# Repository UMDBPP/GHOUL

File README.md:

# GHOUL

Repository for the GHOUL project started in Fall 2022 as a part of the National Eclipse Ballooning Project

(A spooky spiritual sucessor to Helios)

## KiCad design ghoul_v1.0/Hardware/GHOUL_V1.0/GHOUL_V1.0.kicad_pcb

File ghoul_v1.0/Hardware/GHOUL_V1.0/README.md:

View in your browser: https://kicanvas.org/?github=https%3A%2F%2Fgithub.com%2FUMDBPP%2FGHOUL%2Ftree%2Fmain%2Fghoul_v1.0%2FHardware%2FGHOUL_V1.0

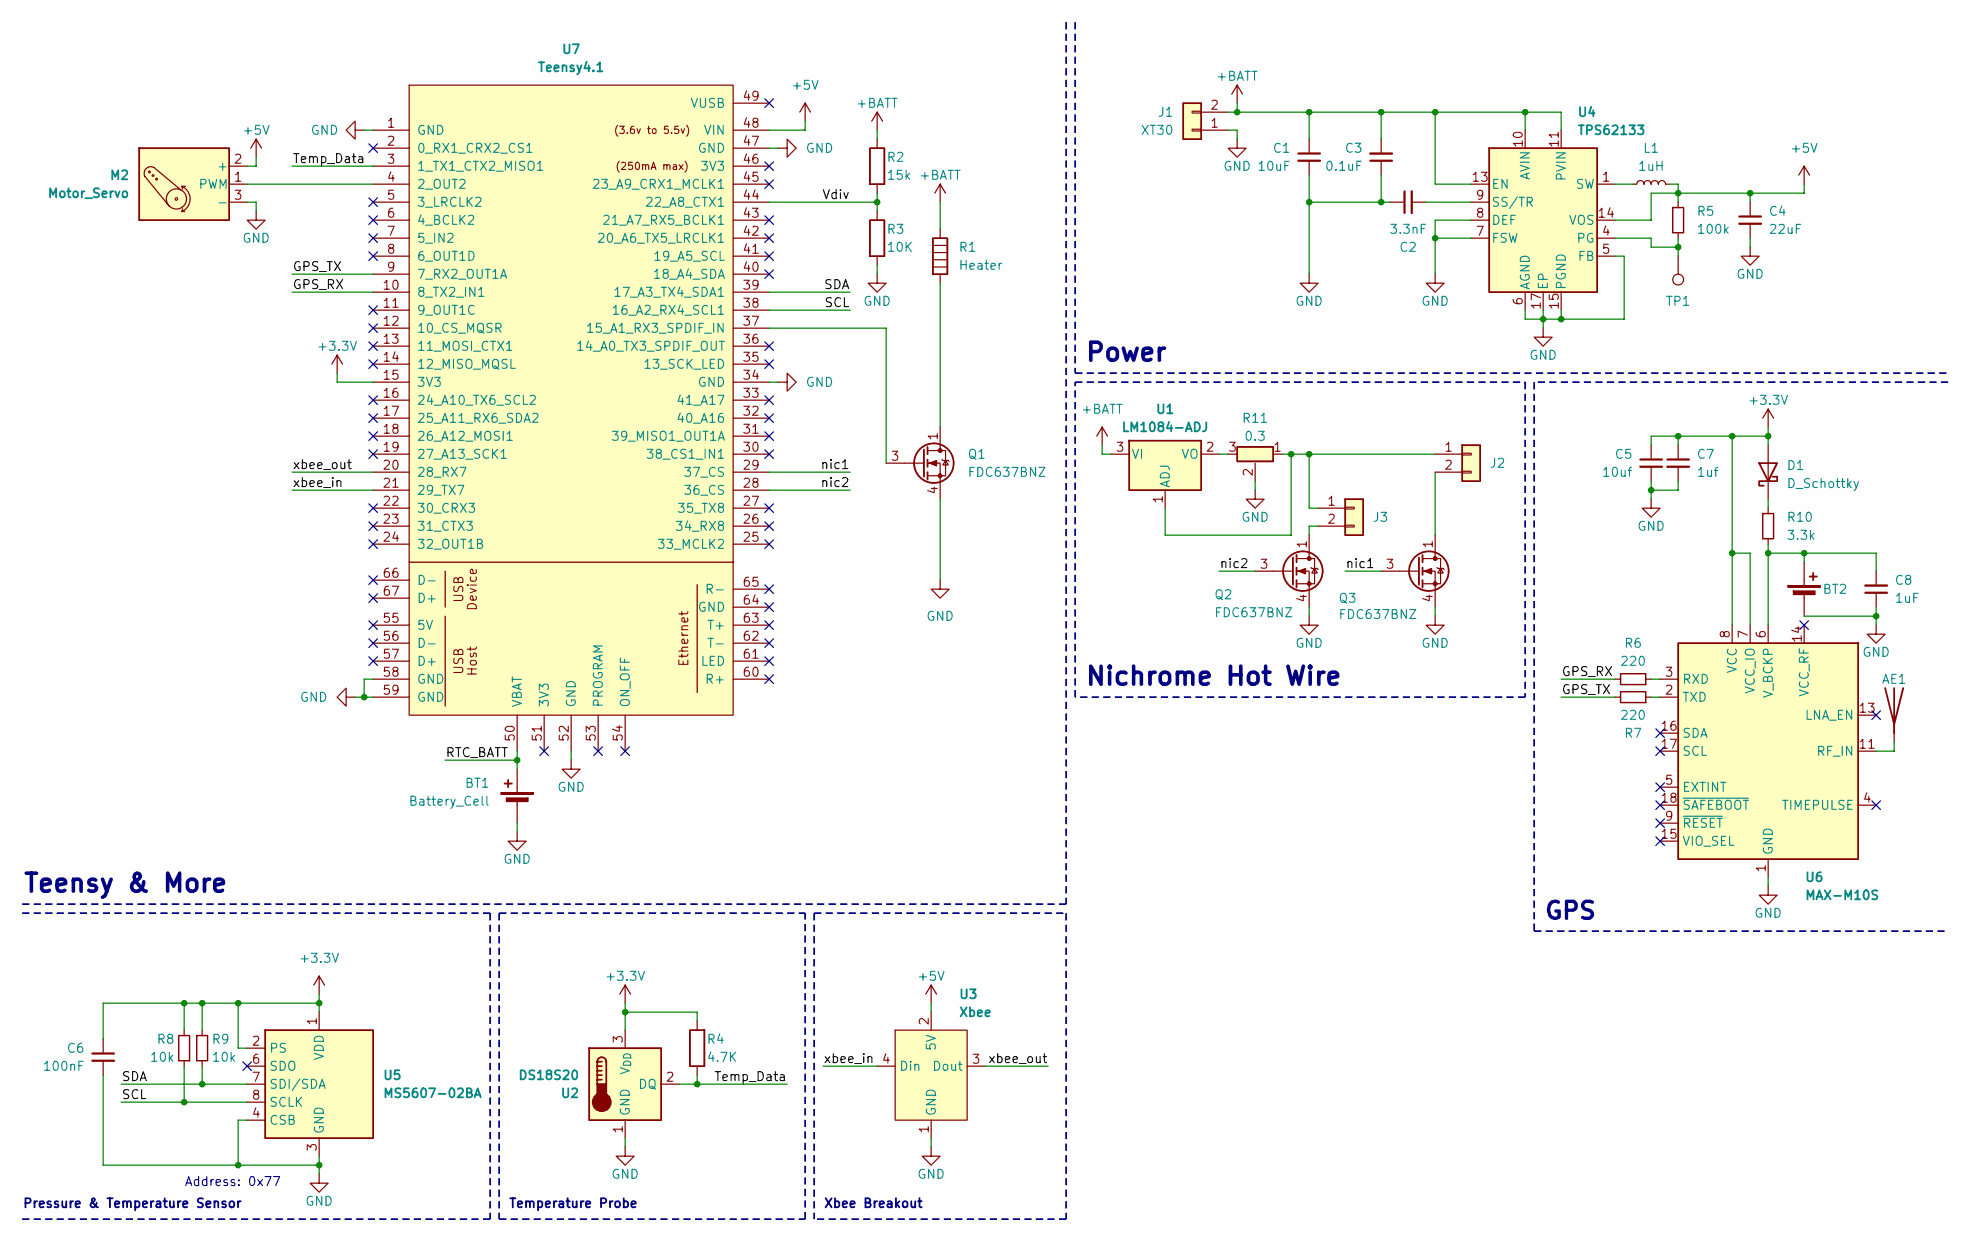
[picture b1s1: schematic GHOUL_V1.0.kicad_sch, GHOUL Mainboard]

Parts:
AE1: 1575AT43A0040001E; ANT_1575AT_JOT-M
BT1: Battery_Cell; BatteryHolder_Keystone_3000_1x12mm
BT2: Battery_Cell; SEIKO_ML414H_IV01E
C1: 10uF; C_0603_1608Metric_Pad1.08x0.95mm_HandSolder
C2: 3.3nF; C_0603_1608Metric_Pad1.08x0.95mm_HandSolder
C3: 0.1uF; C_0603_1608Metric_Pad1.08x0.95mm_HandSolder
C4: 22uF; C_0603_1608Metric_Pad1.08x0.95mm_HandSolder
C5: 10uf; C_0603_1608Metric_Pad1.08x0.95mm_HandSolder
C6: 100nF; C_0603_1608Metric_Pad1.08x0.95mm_HandSolder
C7: 1uf; C_0603_1608Metric_Pad1.08x0.95mm_HandSolder
C8: 1uF; C_0603_1608Metric_Pad1.08x0.95mm_HandSolder
D1: D_Schottky; D_SOD-123F
J1: XT30; AMASS_XT30PW-M_1x02_P2.50mm_Horizontal
J2, J3: Conn_01x02; JST_EH_B2B-EH-A_1x02_P2.50mm_Vertical
L1: 1uH; L_Vishay_IHLP-1212
M2: Motor_Servo; JST_XH_B3B-XH-A_1x03_P2.50mm_Vertical
Q1, Q2, Q3: FDC637BNZ; TSOT-23-6
R1: Heater; JST_EH_B2B-EH-A_1x02_P2.50mm_Vertical
R2: 15k; R_0603_1608Metric
R3: 10K; R_0603_1608Metric
R4: 4.7K; R_0603_1608Metric
R5: 100k; R_0603_1608Metric_Pad0.98x0.95mm_HandSolder
R6, R7: 220; R_0603_1608Metric_Pad0.98x0.95mm_HandSolder
R8, R9: 10k; R_0603_1608Metric_Pad0.98x0.95mm_HandSolder
R10: 3.3k; R_0603_1608Metric_Pad0.98x0.95mm_HandSolder
R11: 0.3; TO-263-2
TP1: TestPoint; TestPoint_Keystone_5000-5004_Miniature
U1: LM1084-ADJ; TO-263-3_TabPin2
U2: DS18S20; JST_EH_B3B-EH-A_1x03_P2.50mm_Vertical
U3: Xbee; XBee Explorer
U4: TPS62133; VQFN-16-1EP_3x3mm_P0.5mm_EP1.68x1.68mm_ThermalVias
U5: MS5607-02BA; LGA-8_3x5mm_P1.25mm
U6: MAX-M10S; ublox_MAX
U7: Teensy4.1; Teensy4_1

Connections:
+3.3V: C5.1, C6.1, C7.1, D1.2 (A), R4.2, R8.2, R9.1, U2.3 (V_{DD}), U5.1 (VDD), U5.2 (PS), U6.7 (VCC_IO), U6.8 (VCC), U7.15 (3V3)
+5V: C4.1, L1.2, M2.2 (+), R5.1, U3.2 (5V), U4.14 (VOS), U7.48 (VIN)
+BATT: C1.1, C3.2, J1.2, R1.1, R2.1, U1.3 (VI), U4.10 (AVIN), U4.11 (PVIN), U4.12 (PVIN), U4.13 (EN)
/GPS_RX: R6.2, U7.10 (8_TX2_IN1)
/GPS_TX: R7.2, U7.9 (7_RX2_OUT1A)
/RTC_BATT: BT1.1 (+), U7.50 (VBAT)
/SCL: R8.1, U5.8 (SCLK), U7.38 (16_A2_RX4_SCL1)
/SDA: R9.2, U5.7 (SDI/SDA), U7.39 (17_A3_TX4_SDA1)
/Temp_Data: R4.1, U2.2 (DQ), U7.3 (1_TX1_CTX2_MISO1)
/Vdiv: R2.2, R3.1, U7.44 (22_A8_CTX1)
/nic1: Q3.3 (G), U7.29 (37_CS)
/nic2: Q2.3 (G), U7.28 (36_CS)
/xbee_in: U3.4 (Din), U7.21 (29_TX7)
/xbee_out: U3.3 (Dout), U7.20 (28_RX7)
GND: BT1.2 (-), BT2.2 (-), C1.2, C2.1, C3.1, C4.2, C5.2, C6.2, C7.2, C8.1, J1.1, M2.3 (-), Q1.4 (S), Q2.4 (S), Q3.4 (S), R3.2, R11.2, U2.1 (GND), U3.1 (GND), U4.5 (FB), U4.6 (AGND), U4.7 (FSW), U4.8 (DEF), U4.15 (PGND), U4.16 (PGND), U4.17 (EP), U5.3 (GND), U5.4 (CSB), U5.5 (CSB), U6.1 (GND), U6.10 (GND), U6.12 (GND), U7.1 (GND), U7.34 (GND), U7.47 (GND), U7.52 (GND), U7.58 (GND), U7.59 (GND)
unnamed: AE1.1 (A), U6.11 (RF_IN)
unnamed: BT2.1 (+), C8.2, R10.2, U6.6 (V_BCKP)
unnamed: D1.1 (K), R10.1
unnamed: J2.1, J3.1, R11.1, U1.1 (ADJ)
unnamed: J2.2, Q3.1 (D), Q3.2 (D), Q3.5 (D), Q3.6 (D)
unnamed: J3.2, Q2.1 (D), Q2.2 (D), Q2.5 (D), Q2.6 (D)
unnamed: L1.1, U4.1 (SW), U4.2 (SW), U4.3 (SW)
unnamed: M2.1 (PWM), U7.4 (2_OUT2)
unnamed: Q1.1 (D), Q1.2 (D), Q1.5 (D), Q1.6 (D), R1.2
unnamed: Q1.3 (G), U7.37 (15_A1_RX3_SPDIF_IN)
unnamed: R11.3, U1.2 (VO)
unnamed: R5.2, TP1.1, U4.4 (PG)
unnamed: C2.2, U4.9 (SS/TR)
unnamed: R6.1, U6.3 (RXD)
unnamed: R7.1, U6.2 (TXD)

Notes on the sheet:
GPS
Power
Pressure & Temperature Sensor
Address: 0x77
Temperature Probe
Nichrome Hot Wire
Teensy & More
Xbee Breakout

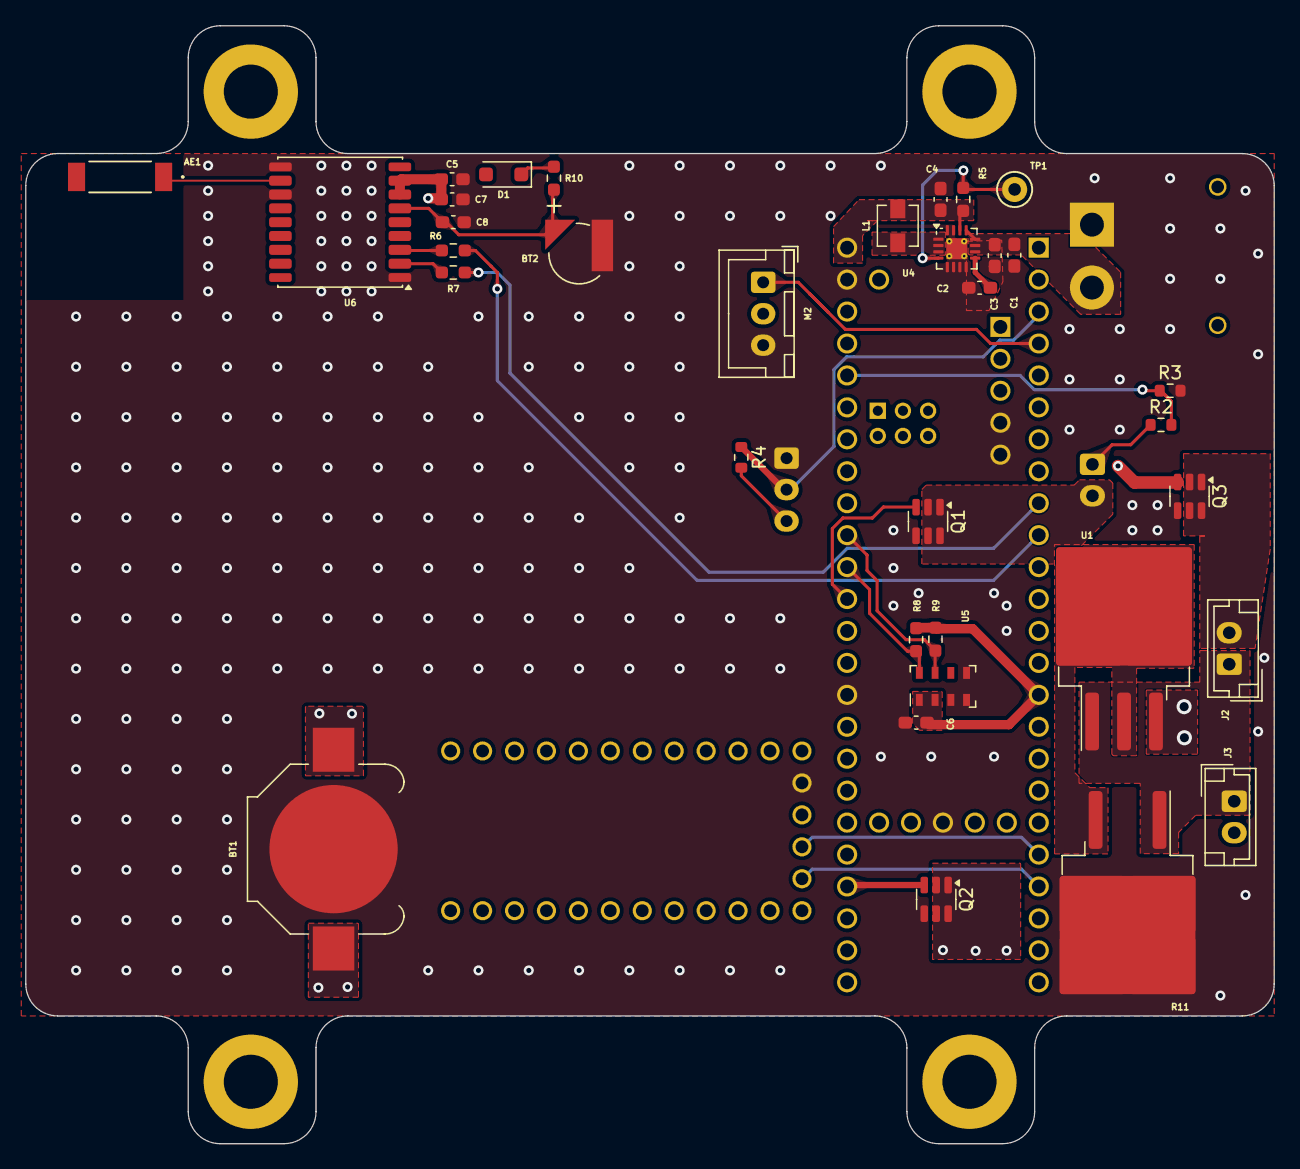
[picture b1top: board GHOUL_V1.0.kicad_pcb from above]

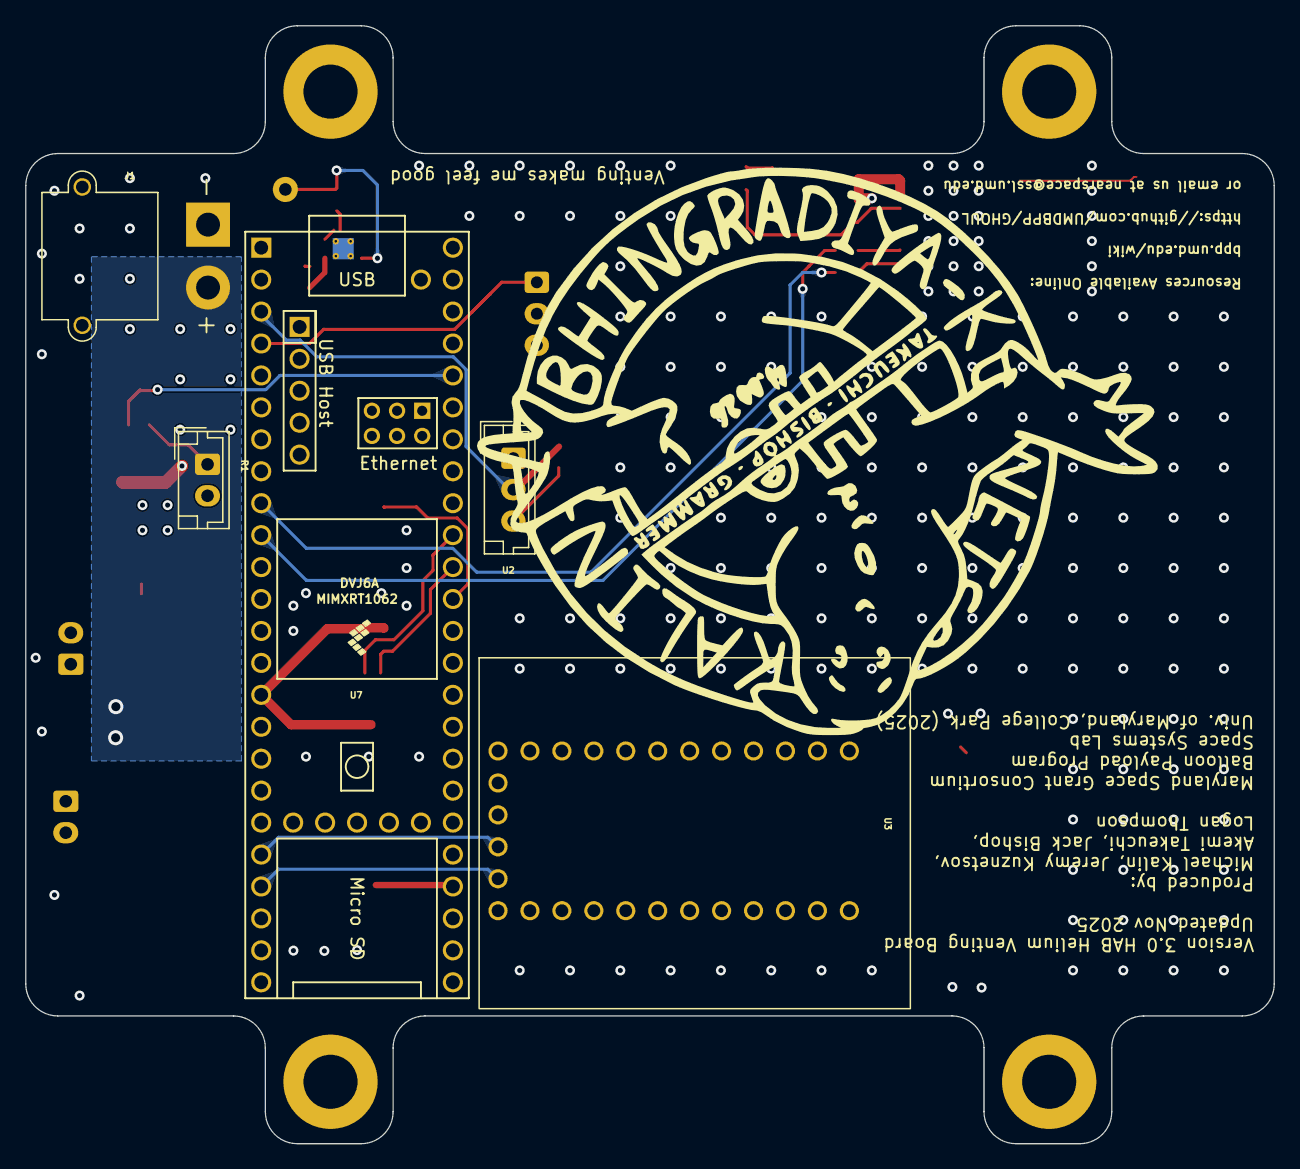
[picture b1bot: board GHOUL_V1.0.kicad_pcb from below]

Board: 4 copper layers, 99.3 x 88.9 mm, 39 parts (5 on the bottom side), 30 nets.

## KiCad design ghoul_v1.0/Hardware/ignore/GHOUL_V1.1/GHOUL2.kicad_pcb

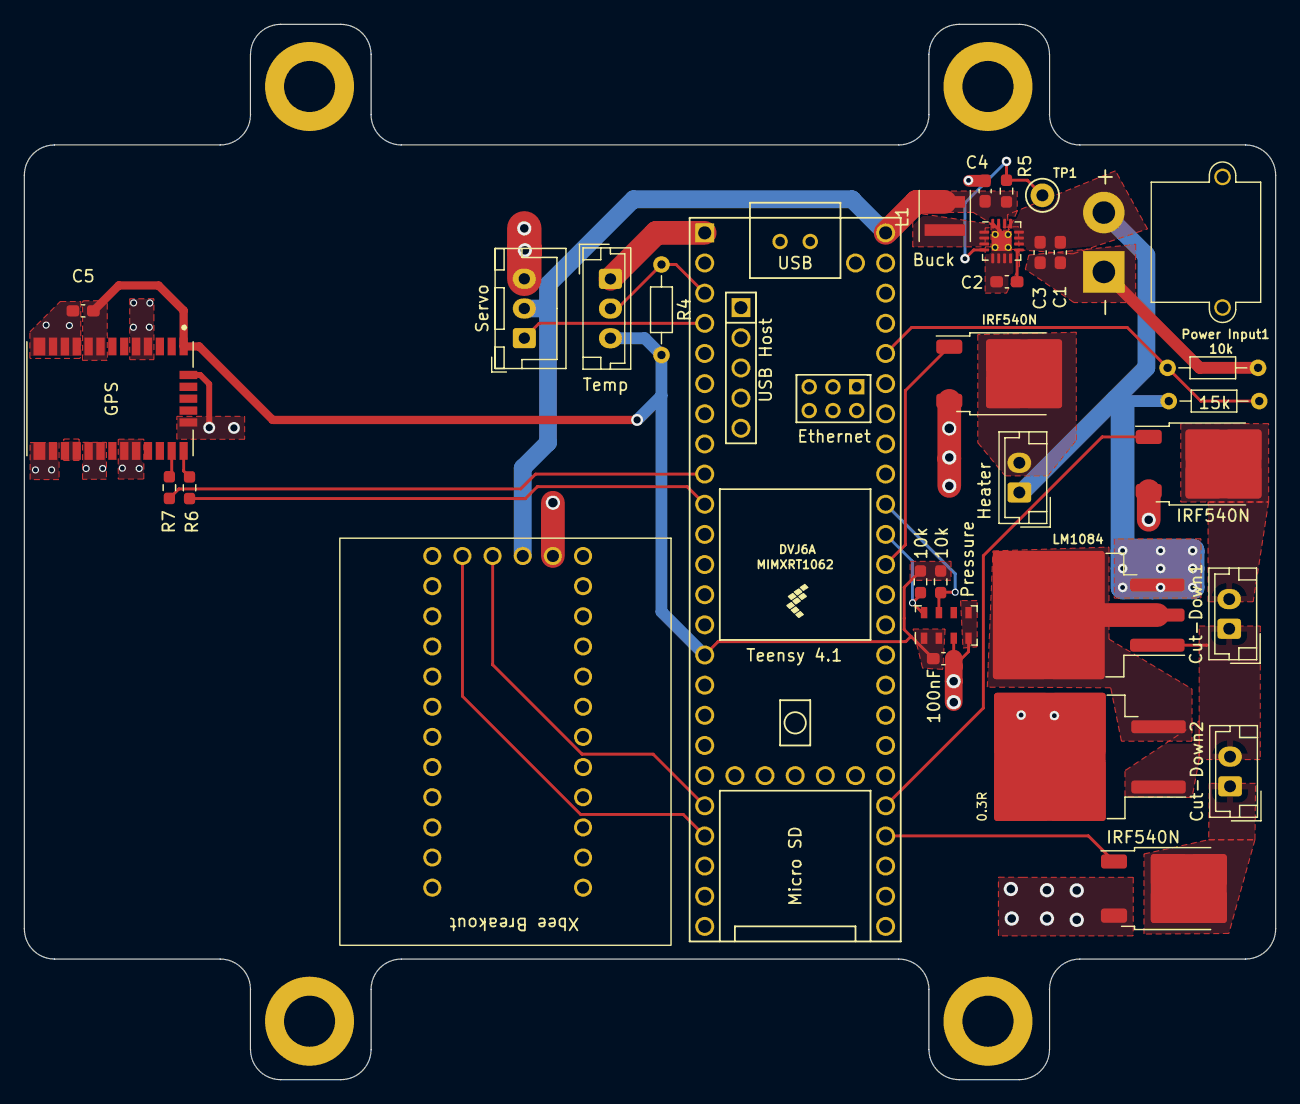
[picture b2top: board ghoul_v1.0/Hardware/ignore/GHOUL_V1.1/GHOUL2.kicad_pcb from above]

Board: 2 copper layers, 105.4 x 88.9 mm, 32 parts (0 on the bottom side), 27 nets.

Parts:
0.3R: 03; TO-263-2
10k, 10k#2: 10k; R_0603_1608Metric_Pad0.98x0.95mm_HandSolder
10k#3: 10K; R_Axial_DIN0204_L3.6mm_D1.6mm_P7.62mm_Horizontal
15k: 15K; R_Axial_DIN0204_L3.6mm_D1.6mm_P7.62mm_Horizontal
100nF: 100nF; C_0603_1608Metric_Pad1.08x0.95mm_HandSolder
Buck: TPS62133; VQFN-16-1EP_3x3mm_P0.5mm_EP1.68x1.68mm_ThermalVias
C1: 10uF; C_0603_1608Metric_Pad1.08x0.95mm_HandSolder
C2: 3.3nF; C_0603_1608Metric_Pad1.08x0.95mm_HandSolder
C3: 0.1uF; C_0603_1608Metric_Pad1.08x0.95mm_HandSolder
C4: 22uF; C_0603_1608Metric_Pad1.08x0.95mm_HandSolder
C5: 4.7uF; C_0603_1608Metric_Pad1.08x0.95mm_HandSolder
Cut-Down1, Cut-Down2: NichromeConnector; JST_EH_B2B-EH-A_1x02_P2.50mm_Vertical
GPS: CAM-M8Q-0; LCC100P960X1400X210-31N
Heater: Heater; JST_EH_B2B-EH-A_1x02_P2.50mm_Vertical
IRF540N, IRF540N#2, IRF540N#3: IRF540N; TO-252-2
L1: 1uH; L_Coilcraft_XxL4040
LM1084: LM1084-ADJ; TO-263-3_TabPin2
Power Input1: Conn_01x02; AMASS_XT30PW-M_1x02_P2.50mm_Horizontal
Pressure: MS5607-02BA; LGA-8_3x5mm_P1.25mm
R4: 4.7K; R_Axial_DIN0204_L3.6mm_D1.6mm_P7.62mm_Horizontal
R5: 100k; R_0603_1608Metric_Pad0.98x0.95mm_HandSolder
R6, R7: 220; R_0603_1608Metric_Pad0.98x0.95mm_HandSolder
Servo: Motor_Servo; JST_XH_B3B-XH-A_1x03_P2.50mm_Vertical
TP1: TestPoint; TestPoint_Keystone_5000-5004_Miniature
Teensy 4.1: Teensy4.1; Teensy41
Temp: DS18S20; JST_EH_B3B-EH-A_1x03_P2.50mm_Vertical
Xbee Breakout: Xbee; XBee Explorer

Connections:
+3.3V: 10k.2, 10k#2.1, 100nF.1, C5.1, GPS.1 (VCC_IO), GPS.8 (V_BCKP), GPS.9 (VCC), Pressure.1 (VDD), Pressure.2 (PS), R4.2, Teensy 4.1.15 (3V3), Temp.3 (V_{DD})
+5V: Buck.14 (VOS), C4.1, L1.2, R5.1, Servo.2 (+), Teensy 4.1.48 (VIN), Xbee Breakout.2 (5V)
+BATT: 15k.1, Buck.10 (AVIN), Buck.11 (PVIN), Buck.12 (PVIN), Buck.13 (EN), C1.1, C3.2, Heater.1, LM1084.3 (VI), Power Input1.2
Baro_SCL: 10k#2.2, Pressure.8 (SCLK), Teensy 4.1.38 (16_A2_RX4_SCL1)
Baro_SDA: 10k.1, Pressure.7 (SDI/SDA), Teensy 4.1.39 (17_A3_TX4_SDA1)
GND: 0.3R.2, 10k#3.2, 100nF.2, Buck.5 (FB), Buck.6 (AGND), Buck.7 (FSW), Buck.8 (DEF), Buck.15 (PGND), Buck.16 (PGND), Buck.17 (EP), C1.2, C2.1, C3.1, C4.2, C5.2, GPS.4 (GND), GPS.5 (GND), GPS.10 (GND), GPS.11 (GND), GPS.12 (GND), GPS.13 (GND), GPS.14 (GND), GPS.15 (GND), GPS.18 (GND), GPS.19 (GND), GPS.21 (GND), GPS.22 (GND), GPS.27 (GND), GPS.31 (GND), IRF540N.3 (S), IRF540N#2.3 (S), IRF540N#3.3 (S), Power Input1.1, Pressure.3 (GND), Pressure.4 (CSB), Pressure.5 (CSB), Servo.3 (-), Teensy 4.1.1 (GND), Temp.1 (GND), Xbee Breakout.1 (Ground)
GPSRx: R6.1, Teensy 4.1.10 (8_TX2_IN1)
GPSTx: R7.2, Teensy 4.1.9 (7_RX2_OUT1A)
unnamed: 0.3R.1, Cut-Down1.1 (In), Cut-Down2.2 (Out), LM1084.1 (ADJ)
unnamed: Cut-Down1.2 (Out), IRF540N.2 (D)
unnamed: Cut-Down2.1 (In), IRF540N#2.2 (D)
unnamed: Buck.1 (SW), Buck.2 (SW), Buck.3 (SW), L1.1
unnamed: 0.3R.3, LM1084.2 (VO)
unnamed: Heater.2, IRF540N#3.2 (D)
unnamed: IRF540N#3.1 (G), Teensy 4.1.37 (15_A1_RX3_SPDIF_IN)
unnamed: GPS.16 (RF_OUT), GPS.17 (RF_IN)
unnamed: GPS.26 (RXD/SPI_MOSI), R6.2
unnamed: GPS.25 (TXD/SPI_MISO), R7.1
unnamed: Buck.4 (PG), R5.2, TP1.1
unnamed: Buck.9 (SS/TR), C2.2
Nic1: IRF540N.1 (G), Teensy 4.1.29 (37_CS)
Nic2: IRF540N#2.1 (G), Teensy 4.1.28 (36_CS)
Servo PWM: Servo.1 (PWM), Teensy 4.1.4 (2_OUT2)
Temp_Data: R4.1, Teensy 4.1.3 (1_TX1_CTX2_MISO1), Temp.2 (DQ)
Vdiv: 10k#3.1, 15k.2, Teensy 4.1.44 (22_A8_CTX1)
Xbee DIn: Teensy 4.1.21 (29_TX7), Xbee Breakout.4 (Din)
Xbee DOut: Teensy 4.1.20 (28_RX7), Xbee Breakout.3 (Dout)

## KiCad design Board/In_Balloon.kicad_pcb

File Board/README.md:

# Main PCB
Here's my attempt of a markdown file for documentation. Here goes!

## Adafruit STMFeatherF405 Express uCon
This is a custom symbol/footprint that I made, so hopefully it's here in this repo. If not, just know that it's a 28 pin symbol and you can refer to [This link](https://www.adafruit.com/product/4382) for pinouts and more about it

## Motor Driver
I forgot the name of the specific motor driver on the PCB, but it's a dual H-Bridge that can control up to 2 stepper motors. **As of right now, this payload uses a servo motor, and is powered through GPIO pins on the uCon**
## GNSS Module MAX M10 GPS
This was pulled from GHOUL. Just know that this is on the I2C bus. Refer to [This Link](https://www.u-blox.com/en/product/max-m10-series) for more info

## Barometer
This is also in the I2C bus. Refer to [This Link](https://www.digikey.com/en/products/detail/te-connectivity-measurement-specialties/MS560702BA03-50/4700921) for more info/anything regarding the schematic

## Everything else
Everything else was basically pulled from GHOUL, which includes the external battery connector, the voltage switcher/regulator component (which just converts external 9V to 5V/3.3V logic for uCon), an XBee radio, temperature probes, and some MOSFET circuits (for the heatpads and Nichrome strips). <br>
The last thing to note is that there's a 3 pin connector for the SPI bus and a connector for the 2nd PCB
# Bert Board
Named after Robert Heng, thanks Robert :) <br>
Baby Bert Board has a barometer (basically same schematic as main PCB), and a 3 pin connector to go back to main PCB. As of 4/29/25, this connection has yet to be soldered.

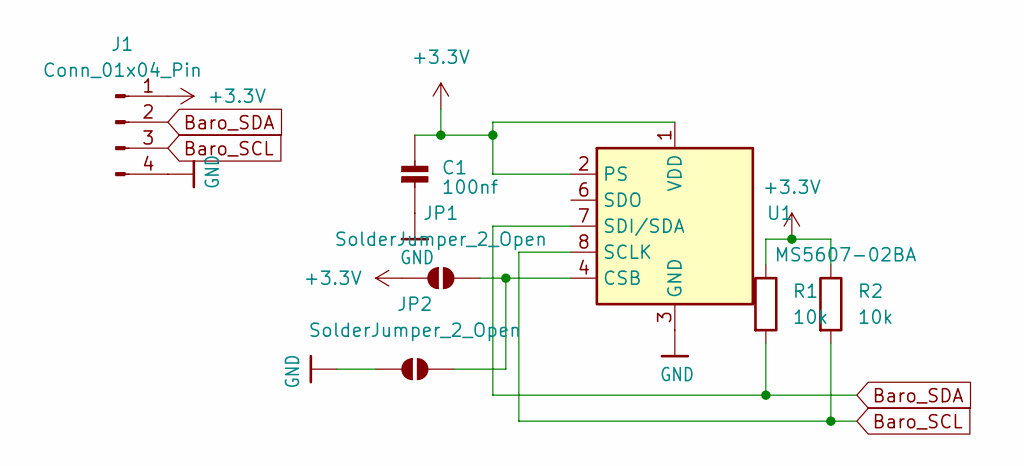
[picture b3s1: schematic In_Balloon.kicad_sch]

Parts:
C1: 100nf; C_0603_1608Metric_Pad1.08x0.95mm_HandSolder
J1: Conn_01x04_Pin; PinHeader_1x04_P1.00mm_Vertical
JP1, JP2: SolderJumper_2_Open; SolderJumper-2_P1.3mm_Open_RoundedPad1.0x1.5mm
R1, R2: 10k; R_0603_1608Metric_Pad0.98x0.95mm_HandSolder
U1: MS5607-02BA; LGA-8_3x5mm_P1.25mm

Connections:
+3.3V: C1.1, J1.1, JP1.1 (A), R1.1, R2.1, U1.1 (VDD), U1.2 (PS)
Baro_SCL: J1.3, R2.2, U1.8 (SCLK)
Baro_SDA: J1.2, R1.2, U1.7 (SDI/SDA)
GND: C1.2, J1.4, JP2.1 (A), U1.3 (GND)
unnamed: JP1.2 (B), JP2.2 (B), U1.4 (CSB), U1.5 (CSB)

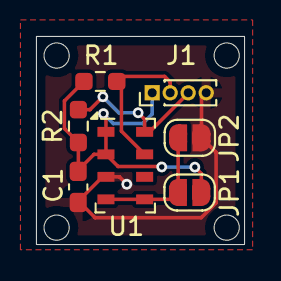
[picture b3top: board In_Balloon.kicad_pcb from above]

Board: 2 copper layers, 11.6 x 11.6 mm, 7 parts (0 on the bottom side), 5 nets.

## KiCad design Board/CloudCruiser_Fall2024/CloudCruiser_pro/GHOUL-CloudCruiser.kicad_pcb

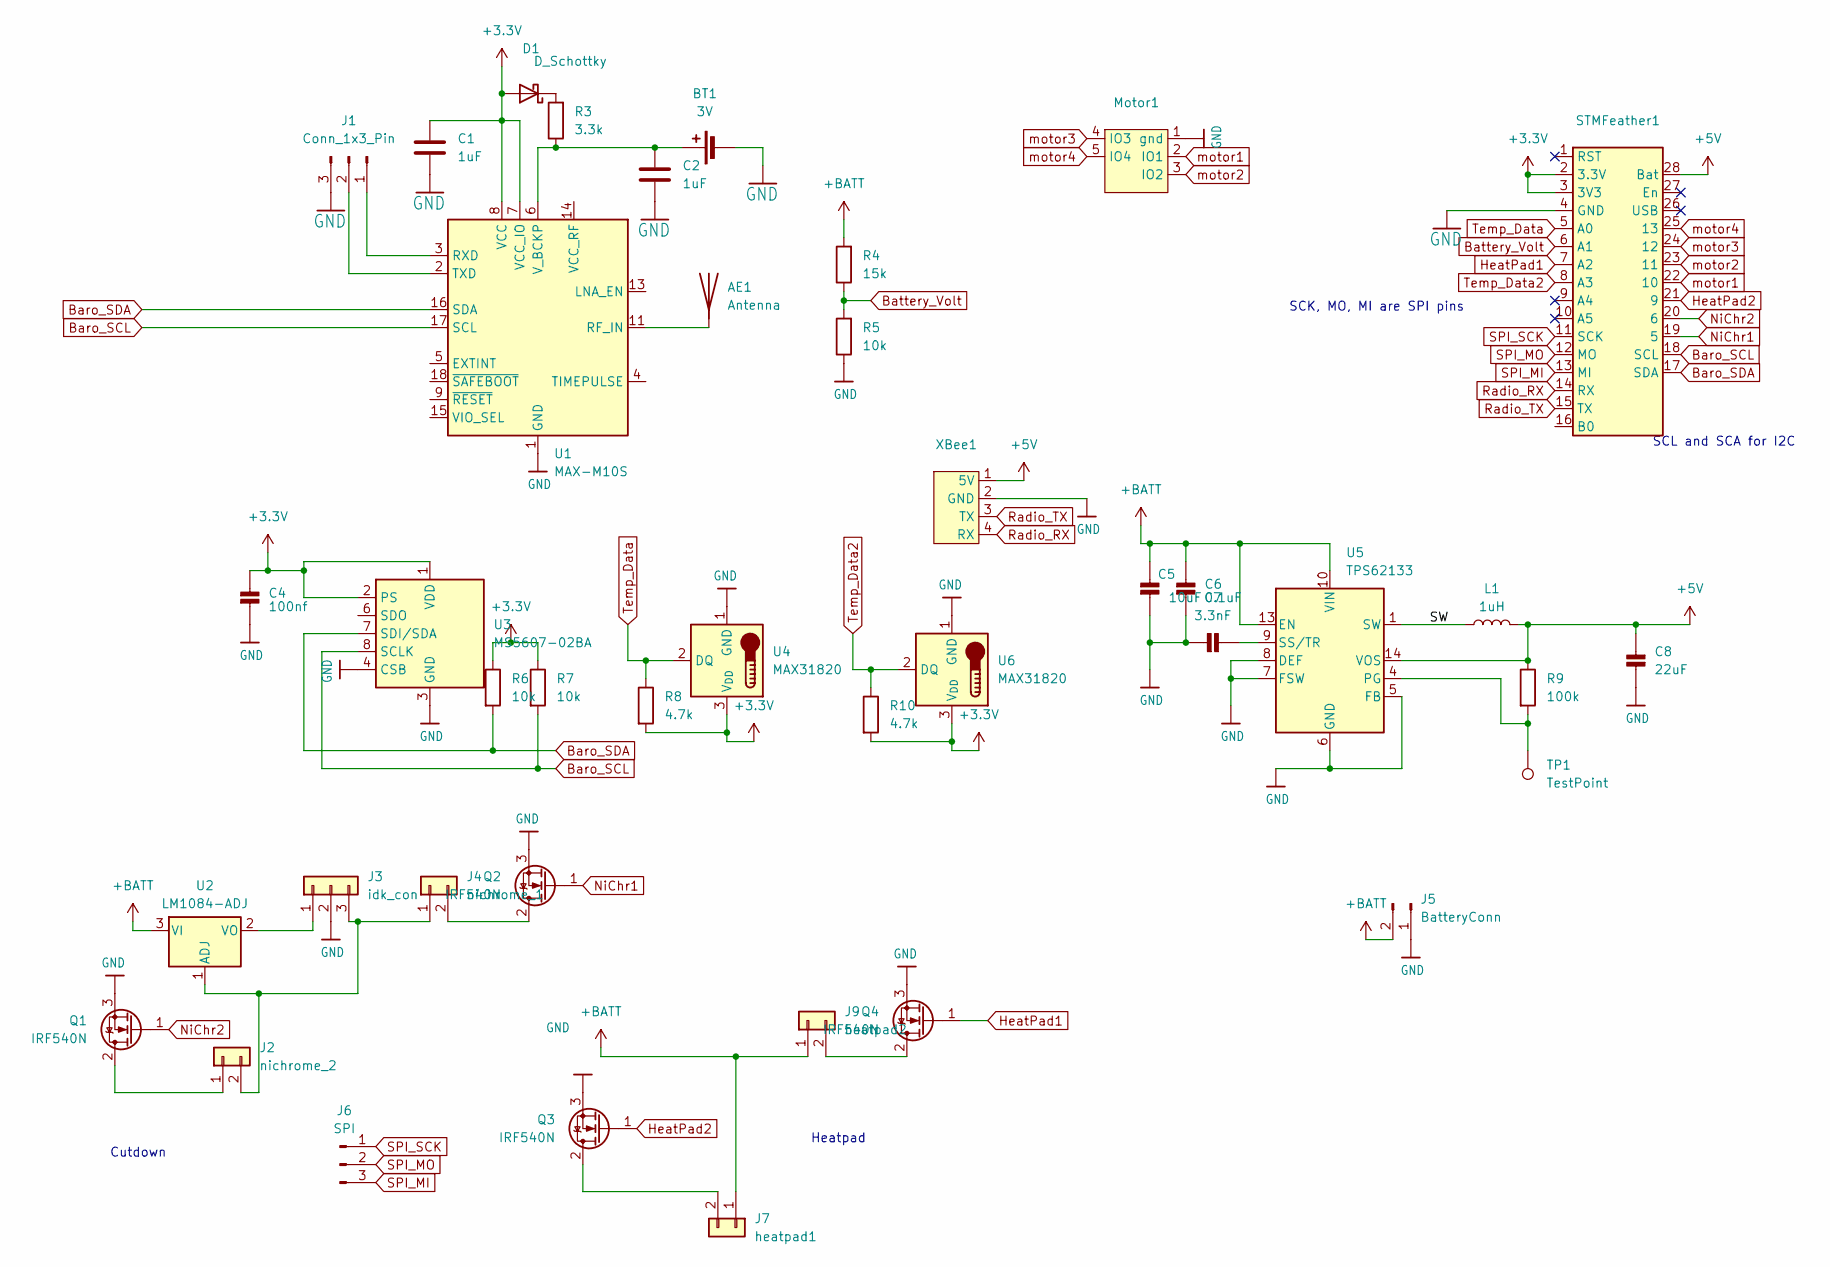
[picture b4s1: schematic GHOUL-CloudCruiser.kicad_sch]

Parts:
AE1: Antenna; ANT_1575AT_JOT-M
BT1: 3V; SEIKO_ML414H_IV01E
C1, C2: 1uF; C_0603_1608Metric_Pad1.08x0.95mm_HandSolder
C4: 100nf; C_0603_1608Metric_Pad1.08x0.95mm_HandSolder
C5: 10uF; C_0805_2012Metric_Pad1.18x1.45mm_HandSolder
C6: 0.1uF; C_0603_1608Metric_Pad1.08x0.95mm_HandSolder
C7: 3.3nF; C_0603_1608Metric_Pad1.08x0.95mm_HandSolder
C8: 22uF; C_0805_2012Metric_Pad1.18x1.45mm_HandSolder
D1: D_Schottky; D_SOD-123F
J1: Conn_1x3_Pin; PinHeader_1x03_P2.54mm_Vertical
J2: nichrome_2; PinHeader_1x02_P2.54mm_Vertical
J3: idk_con; TO-263-2
J4: nichrome_1; PinHeader_1x02_P2.54mm_Vertical
J5: BatteryConn; PinHeader_1x02_P2.54mm_Vertical
J6: SPI; PinHeader_1x03_P2.54mm_Vertical
J7: heatpad1; PinHeader_1x02_P2.54mm_Vertical
J9: heatpad2; PinHeader_1x02_P2.54mm_Vertical
L1: 1uH; L_Coilcraft_XxL4040
Motor1: PinHeader_1x05_P2.54mm_Vertical
Q1, Q2, Q3, Q4: IRF540N; TO-220-3_Vertical
R3: 3.3k; R_0603_1608Metric_Pad0.98x0.95mm_HandSolder
R4: 15k; R_0603_1608Metric_Pad0.98x0.95mm_HandSolder
R5, R6, R7: 10k; R_0603_1608Metric_Pad0.98x0.95mm_HandSolder
R8, R10: 4.7k; R_0603_1608Metric_Pad0.98x0.95mm_HandSolder
R9: 100k; R_0603_1608Metric_Pad0.98x0.95mm_HandSolder
STMFeather1: Adafruit_FeatherSTM32F405
TP1: TestPoint; TestPoint_Keystone_5000-5004_Miniature
U1: MAX-M10S; ublox_MAX
U2: LM1084-ADJ; TO-263-3_TabPin2
U3: MS5607-02BA; LGA-8_3x5mm_P1.25mm
U4, U6: MAX31820; TO-92_Inline
U5: TPS62133; VQFN-16-1EP_3x3mm_P0.5mm_EP1.68x1.68mm_ThermalVias
XBee1: PinHeader_1x04_P2.54mm_Vertical

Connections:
+3.3V: C1.1, C4.1, D1.2 (A), R6.1, R7.1, R8.2, R10.2, STMFeather1.2 (3.3V), STMFeather1.3 (3V3), U1.7 (VCC_IO), U1.8 (VCC), U3.1 (VDD), U3.2 (PS), U4.3 (V_{DD}), U6.3 (V_{DD})
+5V: C8.2, L1.2, R9.1, STMFeather1.28 (Bat), U5.14 (VOS), XBee1.1 (5V)
+BATT: C5.1, C6.1, J5.2, J7.1, J9.1, R4.2, U2.3 (VI), U5.10 (VIN), U5.11 (VIN), U5.12 (VIN), U5.13 (EN)
/SW: L1.1, U5.1 (SW), U5.2 (SW), U5.3 (SW)
Baro_SCL: R7.2, STMFeather1.18 (SCL), U1.17 (SCL), U3.8 (SCLK)
Baro_SDA: R6.2, STMFeather1.17 (SDA), U1.16 (SDA), U3.7 (SDI/SDA)
Battery_Volt: R4.1, R5.2, STMFeather1.6 (A1)
GND: BT1.2 (-), C1.2, C2.2, C4.2, C5.2, C6.2, C7.1, C8.1, J1.3, J3.2, J5.1, Motor1.1 (gnd), Q1.3 (S), Q2.3 (S), Q3.3 (S), Q4.3 (S), R5.1, STMFeather1.4 (GND), U1.1 (GND), U1.10 (GND), U1.12 (GND), U3.3 (GND), U3.4 (CSB), U3.5 (CSB), U4.1 (GND), U5.5 (FB), U5.6 (GND), U5.7 (FSW), U5.8 (DEF), U5.15 (GND), U5.16 (GND), U5.17 (GND), U6.1 (GND), XBee1.2 (GND)
HeatPad1: Q4.1 (G), STMFeather1.7 (A2)
HeatPad2: Q3.1 (G), STMFeather1.21 (9)
unnamed: AE1.1 (A), U1.11 (RF_IN)
unnamed: BT1.1 (+), C2.1, R3.1, U1.6 (V_BCKP)
unnamed: D1.1 (K), R3.2
unnamed: J1.1, U1.3 (RXD)
unnamed: J1.2, U1.2 (TXD)
unnamed: J2.1, Q1.2 (D)
unnamed: J2.2, J3.3, J4.1, U2.1 (ADJ)
unnamed: J3.1, U2.2 (VO)
unnamed: J4.2, Q2.2 (D)
unnamed: J7.2, Q3.2 (D)
unnamed: J9.2, Q4.2 (D)
unnamed: R9.2, TP1.1, U5.4 (PG)
unnamed: C7.2, U5.9 (SS/TR)
NiChr1: Q2.1 (G), STMFeather1.19 (5)
NiChr2: Q1.1 (G), STMFeather1.20 (6)
Radio_RX: STMFeather1.14 (RX), XBee1.4 (RX)
Radio_TX: STMFeather1.15 (TX), XBee1.3 (TX)
SPI_MI: J6.3, STMFeather1.13 (MI)
SPI_MO: J6.2, STMFeather1.12 (MO)
SPI_SCK: J6.1, STMFeather1.11 (SCK)
Temp_Data: R8.1, STMFeather1.5 (A0), U4.2 (DQ)
Temp_Data2: R10.1, STMFeather1.8 (A3), U6.2 (DQ)
motor1: Motor1.2 (IO1), STMFeather1.22 (10)
motor2: Motor1.3 (IO2), STMFeather1.23 (11)
motor3: Motor1.4 (IO3), STMFeather1.24 (12)
motor4: Motor1.5 (IO4), STMFeather1.25 (13)

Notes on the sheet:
Heatpad
Cutdown
SCL and SCA for I2C
SCK, MO, MI are SPI pins

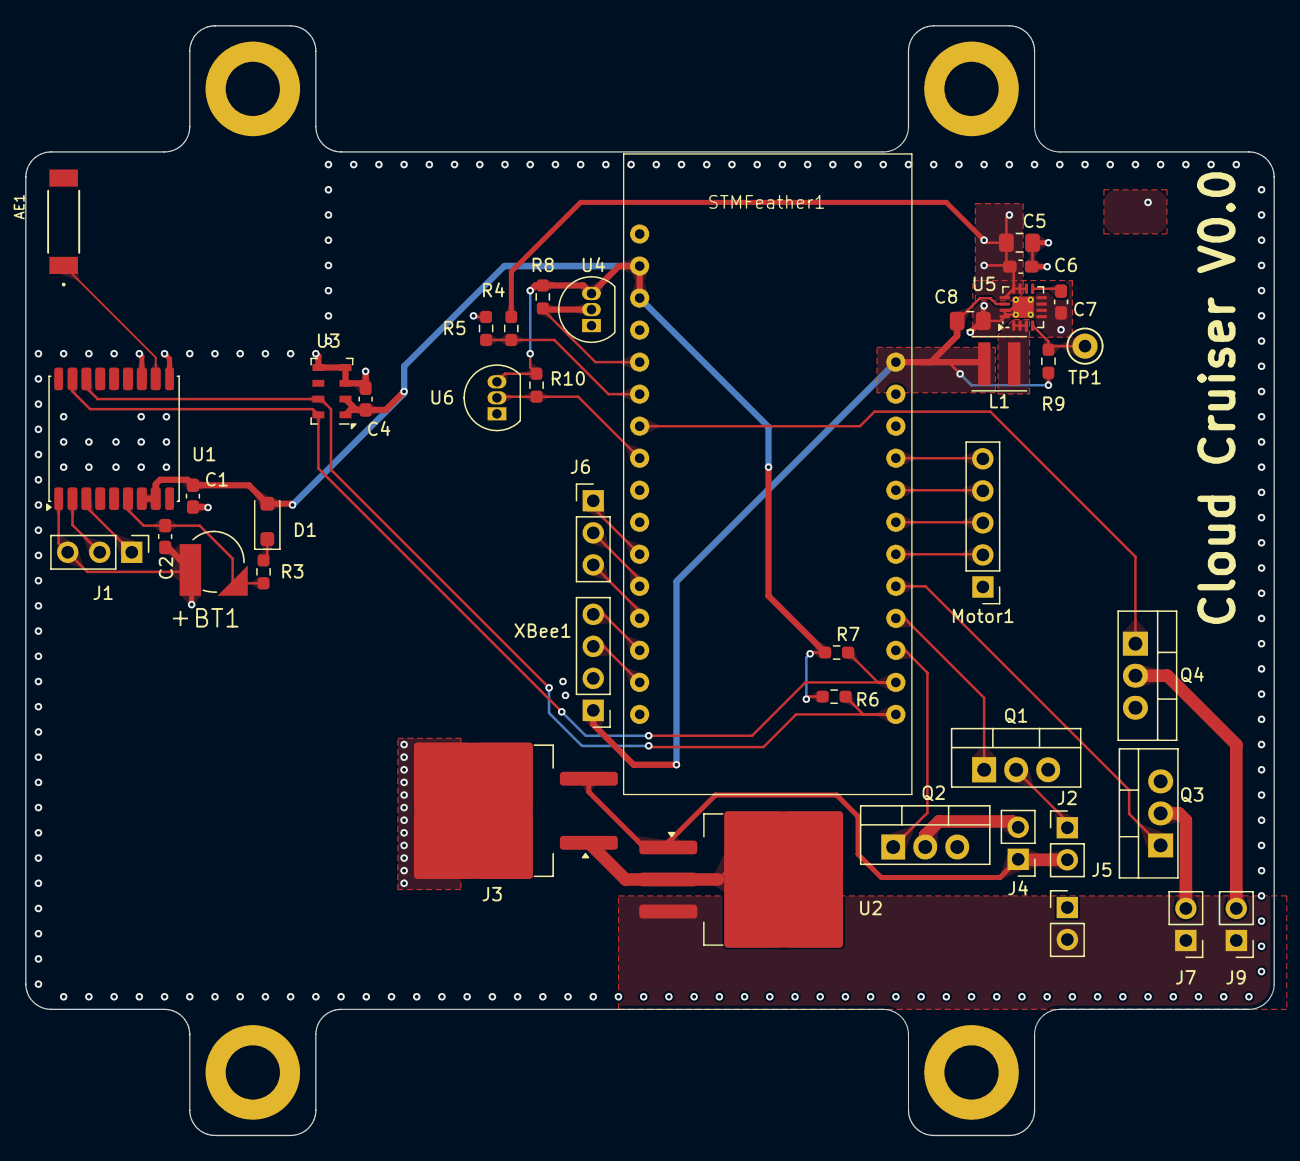
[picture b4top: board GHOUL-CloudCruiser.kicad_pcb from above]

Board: 4 copper layers, 99.0 x 88.0 mm, 41 parts (0 on the bottom side), 36 nets.

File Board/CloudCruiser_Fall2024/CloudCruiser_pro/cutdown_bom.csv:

"Reference","Value","Datasheet","Footprint","Qty","DNP"
"AE1","Antenna","~","CloudCruiser_footprint:ANT_1575AT_JOT-M","1",""
"BT1","3V","~","CloudCruiser_footprint:SEIKO_ML414H_IV01E","1",""
"C1,C2","1uF","~","Capacitor_SMD:C_0603_1608Metric_Pad1.08x0.95mm_HandSolder","2",""
"C4","100nf","","Capacitor_SMD:C_0603_1608Metric_Pad1.08x0.95mm_HandSolder","1",""
"C5","10uF","","Capacitor_SMD:C_0805_2012Metric_Pad1.18x1.45mm_HandSolder","1",""
"C6","0.1uF","","Capacitor_SMD:C_0603_1608Metric_Pad1.08x0.95mm_HandSolder","1",""
"C7","3.3nF","","Capacitor_SMD:C_0603_1608Metric_Pad1.08x0.95mm_HandSolder","1",""
"C8","22uF","","Capacitor_SMD:C_0805_2012Metric_Pad1.18x1.45mm_HandSolder","1",""
"D1","D_Schottky","~","Diode_SMD:D_SOD-123F","1",""
"J1","Conn_1x3_Pin","~","Connector_PinHeader_2.54mm:PinHeader_1x03_P2.54mm_Vertical","1",""
"J2","nichrome_2","~","Connector_PinHeader_2.54mm:PinHeader_1x02_P2.54mm_Vertical","1",""
"J3","idk_con","~","Package_TO_SOT_SMD:TO-263-2","1",""
"J4","nichrome_1","~","Connector_PinHeader_2.54mm:PinHeader_1x02_P2.54mm_Vertical","1",""
"J5","BatteryConn","~","Connector_PinHeader_2.54mm:PinHeader_1x02_P2.54mm_Vertical","1",""
"J6","SPI","~","Connector_PinHeader_2.54mm:PinHeader_1x03_P2.54mm_Vertical","1",""
"J7","heatpad1","~","Connector_PinHeader_2.54mm:PinHeader_1x02_P2.54mm_Vertical","1",""
"J9","heatpad2","~","Connector_PinHeader_2.54mm:PinHeader_1x02_P2.54mm_Vertical","1",""
"L1","1uH","~","Inductor_SMD:L_Coilcraft_XxL4040","1",""
"Motor1,STMFeather1,XBee1","~","","-- mixed values --","3",""
"Q1,Q2,Q3,Q4","IRF540N","http://www.irf.com/product-info/datasheets/data/irf540n.pdf","Package_TO_SOT_THT:TO-220-3_Vertical","4",""
"R3","3.3k","~","Resistor_SMD:R_0603_1608Metric_Pad0.98x0.95mm_HandSolder","1",""
"R4","15k","~","Resistor_SMD:R_0603_1608Metric_Pad0.98x0.95mm_HandSolder","1",""
"R5,R6,R7","10k","~","Resistor_SMD:R_0603_1608Metric_Pad0.98x0.95mm_HandSolder","3",""
"R8,R10","4.7k","~","Resistor_SMD:R_0603_1608Metric_Pad0.98x0.95mm_HandSolder","2",""
"R9","100k","~","Resistor_SMD:R_0603_1608Metric_Pad0.98x0.95mm_HandSolder","1",""
"TP1","TestPoint","~","TestPoint:TestPoint_Keystone_5000-5004_Miniature","1",""
"U1","MAX-M10S","https://content.u-blox.com/sites/default/files/MAX-M10S_Data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","RF_GPS:ublox_MAX","1",""
"U2","LM1084-ADJ","http://www.ti.com/lit/ds/symlink/lm1084.pdf","Package_TO_SOT_SMD:TO-263-3_TabPin2","1",""
"U3","MS5607-02BA","https://www.te.com/commerce/DocumentDelivery/DDEController?A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","Package_LGA:LGA-8_3x5mm_P1.25mm","1",""
"U4,U6","MAX31820","http://datasheets.maximintegrated.com/en/ds/MAX31820.pdf","Package_TO_SOT_THT:TO-92_Inline","2",""
"U5","TPS62133","http://www.ti.com/lit/ds/symlink/tps62130.pdf","Package_DFN_QFN:VQFN-16-1EP_3x3mm_P0.5mm_EP1.68x1.68mm_ThermalVias","1",""

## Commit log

2022-12-03 ns114 code
2022-12-03 rebranding for ns114
2022-12-03 updated code
2022-12-03 flight code ready!
2022-12-03 finished testing ns114
2022-12-03 finished flight code ns114?
2022-12-04 updated libraries
2022-12-04 gps branch
2022-12-04 ns114 flight data, code, and testing code
2023-01-02 made gitignore for kicad stuff
2023-01-02 Added Board.
2023-01-03 did a layout, needs some more work but at least it exists now
2023-01-03 fixed goofy-ah xbee foorprint
2023-01-03 fixed goofy-ah xbee footprint (sch update)
2023-01-04 sometimes the fastest way to get to the end is to throw everything out and start over
2023-01-04 fixed some routing
2023-01-04 progress
2023-01-05 lots of improvements
2023-01-07 finished layout for pcb v2 first draft
2023-01-09 made it way more complicated, in a good way?
2023-01-09 got rid of gbrs
2023-01-10 Rounded Corners but not mounting holes
2023-01-13 Added mounting, labels, rounded corners
2023-01-13 Rounded tab edges
2023-01-15 work in progress...
2023-01-16 cleaned up some things
2023-01-16 i think we are pretty close to being done
2023-01-16 for real this time... ?
2023-01-16 done for now, not because its necesarily done but because im tired
2023-01-16 Finished up fixed kalins silly error deleting all my cool labels
2023-01-16 made gps work?
2023-01-16 gps functionality cut-down test
2023-01-16 print statements
2023-01-17 tidying and labeling - not solved the 10s issue yet
2023-01-17 println:
2023-01-17 diagnostic stuff
2023-01-17 Geofence is working
2023-01-29 updated pin definitions
2023-01-30 updated code for new board
2023-01-30 fixed schematic and brd bmp280 miswiring
2023-02-04 working on ghoul code
2023-02-09 Added counters to primary cut-down triggers (not timer)
2023-03-01 updates for ns115
2023-03-04 added xbee stuff
2023-03-14 added data from flight, made some minor post-flight code edits
2023-03-17 Schematic clarity improvements
2023-03-27 ns116 testing
2023-03-28 updates to code and data
2023-03-31 added freezer test data
2023-04-06 old owrk
2023-04-06 removed open close functions
2023-05-24 updated brd
2023-05-25 updated jb's errors
2023-05-25 removed g***
2023-05-27 fixed jb's poor job
2023-05-27 fixed more of JB's mistakes
2023-05-27 added the volrage variables nad updated pins for new biard
2023-05-27 akemi's awesome code updates
2023-05-27 fixed akemis mistakes
2023-05-27 got rid of dumb print statements
2023-05-27 got rid of typo
2023-06-02 ns118 updates
2023-06-02 starting adding dynamic timer functionality
2023-06-02 started to add dyanmic open timer
2023-06-02 added dynamic venting timer
2023-06-02 added manual vent timer to ground station comms
2023-06-02 made more mistakes, but workable now
2023-06-04 fixed mistakes
2023-06-04 thinks it could work lol, to be tested
2023-06-04 added testing parameter
2023-06-04 IT WORKS
2023-06-04 updated serial commands
2023-06-04 fixed open issues
2023-07-20 added ns119
2023-07-21 added dynamic timed commands
2023-08-31 added gps, buck, pressure and clean up
2023-08-31 changes lol
2023-09-01 shipman fix it
2023-09-01 shipman please fix it
2023-09-01 mostly fixed
2023-09-01 Ordering
2023-09-15 board redesign code
2023-09-15 test
2023-09-16 trying to make work
2023-09-16 more
2023-09-16 ns121 code changes
2023-09-23 added SAM and changed PCB
2023-09-23 added teensy rtc
2023-09-25 added 3.3V gps fill
2023-09-25 decoupling and gps batt
2023-09-25 added gps batt and via stitch
2023-09-25 fixed caps and things
2023-09-25 fixed more things
2023-09-26 saved new things
2023-09-26 batt pad to bot layer
2023-10-09 libraries
2023-11-26 Ghoul paper docs
2023-11-26 added paper documents
2023-11-26 added all data for ns117-ns122
2023-11-26 finished all graphs except ns 112
2023-11-27 added latest graphs, fixing ns115
2024-02-02 started GHOUL 2024.0
2024-02-02 kicad-lib new footprints
2024-02-02 added notes to GHOUL 2024.0
2024-02-02 test cutdown board schematic almost done, need to add sim and layout
2024-02-03 ready to order Cutdown Test
2024-02-03 sync
2024-02-04 added buck converter to logic board
2024-02-04 minor cutdown circuit tuning
2024-02-04 sim results
2024-02-04 started layout
2024-02-04 starting board layout
2024-02-05 finished connecting everything
2024-02-05 ordered cutdown test board, more work on Babel fish
2024-02-06 kicad-lib updates
2024-02-06 Babel Fish ready for layout
2024-02-06 started routing Babel Fish
2024-02-06 more Babel fish routing
2024-02-07 finished board
2024-02-07 Finished board outline
2024-02-07 ready for shipman review
2024-02-07 almost as good as garlic honey chicken
2024-02-07 your mom
2024-02-07 did your mom
2024-02-07 babel fish more routing work
2024-02-07 added DS_Store to gitignore
2024-02-08 ordered GHOUL 2024.0
2024-02-09 created 2024.0 firmware, includes initial servo code
2024-02-09 servo resolution now 3x
2024-02-09 documented servo drive code
2024-02-10 more servo code, nice open and close now with optional low power mode
2024-02-13 removed dumb disable_servo() delay
2024-03-09 skeleton of GHOUL 2024.0 flight code
2024-03-10 radio testing, working at full power
2024-03-14 flight code updates and improved readability
2024-03-14 new executable name
2024-03-14 board updates
2024-03-14 updated radio library
2024-03-14 fixed some mistakes with acks
2024-03-15 vent commands
2024-03-15 gps time parsing and logging works
2024-03-15 hopefully final changes for NS-125
2024-03-15 minor changes
2024-10-03 random demo change
2024-10-10 updated gitignore to remove DS_Store bloat
2024-11-25 Andy Ngo - Final KiCad and Arduino products for Fall 2024 Semester
2025-02-10 cleaned up reversion schematic, need to continue fixing PCB layout due to naming conflicts, should be more readable now though
2025-02-10 deleted duplicate directory
2025-02-10 added V1.0 kicad project readme with canvas link
2025-02-26 added Akemi's secret version
2025-03-04 shuffling things around
2025-03-04 almost have V1.0 cleaned up
2025-04-06 switched GPS received, added via stitching, axial R to SMD
2025-04-17 Add files via upload
    ns133
2025-04-30 Rename CloudCruiser_Board_README.md to README.md
2025-07-28 started playing with ns120 data to develop a FIR filter for ascent rate and then a PI(D) loop to control ascent rate with vent open time
2025-07-28 added first order IIR filter because that's probably good enough for us and uses less processing time
2025-07-29 further developed sim for I loop (no P or D lol) and wrote some python to graph it
2025-07-29 switched to altitude control loop
2025-07-29 altitude outer loop, ascent rate inner loop P control
2025-07-30 refactor and reorg
2025-07-30 added readme
2025-07-30 updated sim readme and added simple non-linear ascent rate to the sim
2025-07-30 added example output to readme
2025-07-30 example image
2025-10-30 akemi testing git
2025-10-30 correct BOM for ordering parts
2025-10-31 final akemi changes
2025-10-31 ignore all DS_Store
2025-10-31 minor pid sim changes
2025-10-31 kicad-lib updates for V1.0
2025-10-31 fixed some minor DRC errors, shortened length to reduce manufacture cost
2025-12-27 remove kicad lib submodule
2025-12-27 remove some old folders
